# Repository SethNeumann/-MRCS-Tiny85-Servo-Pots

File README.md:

# REPO NAME: MRCS-Tiny85-Servo-Pots

## License: Creative Commons Attribution-NonCommercial-ShareAlike

A simple servo controller to replace Mark Schutzer's PIC based design for which the PIC has become unavbailable.
This controls an SG90 or similar low cost servo. End travel positions are set with 2 pots.  There is a single
input line which is grounded to reverse the turnout. An onboard push button is provided to easy calibration. In
addition to the servo output a LED is provided with onboard limiting resistor.

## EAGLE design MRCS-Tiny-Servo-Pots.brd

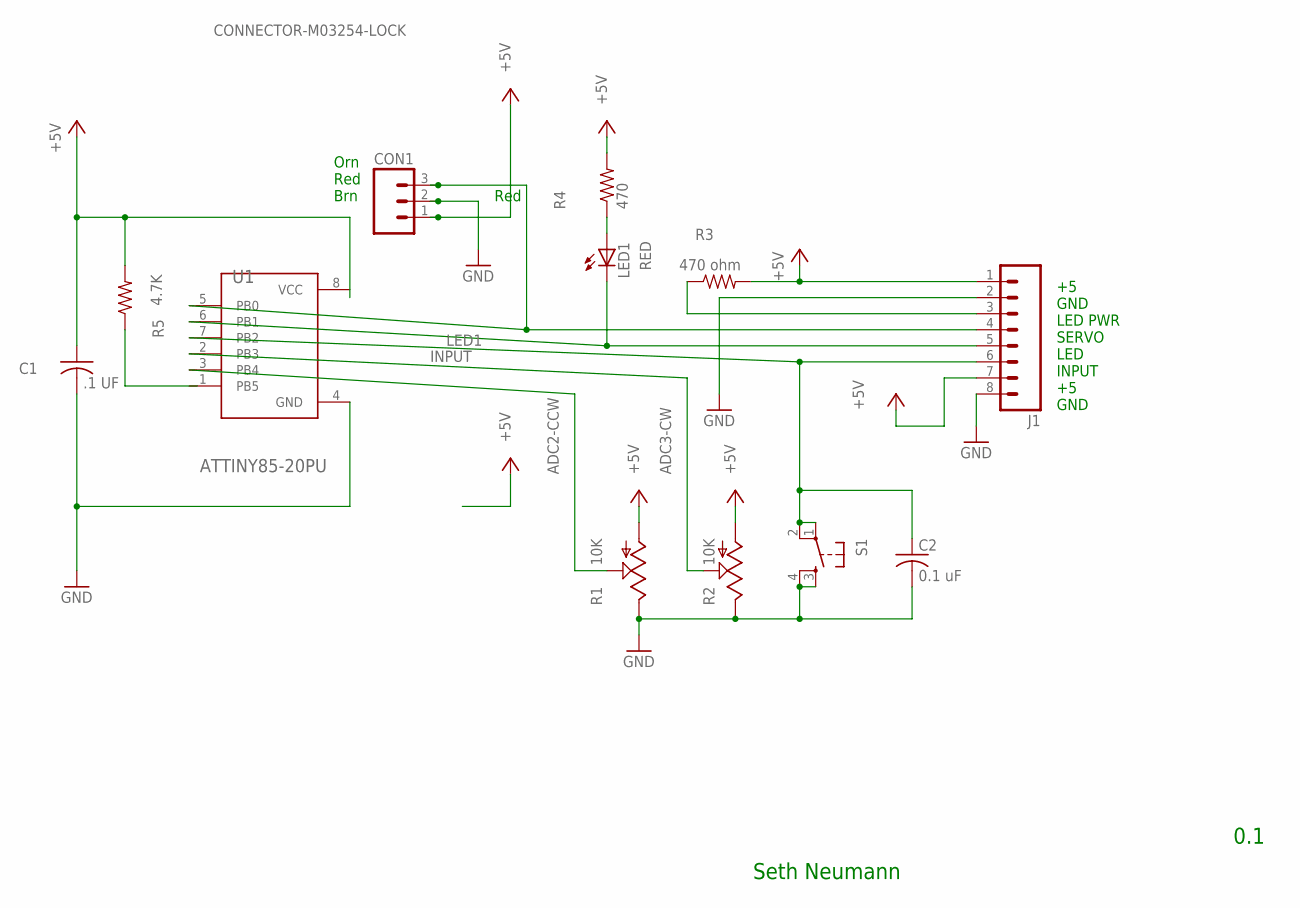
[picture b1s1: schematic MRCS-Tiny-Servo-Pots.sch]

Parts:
C1: .1 UF; C-PTH-0.100
C2: 0.1 uF; C-PTH-0.100
CON1: CONNECTOR-M03254-LOCK; 3POL254
J1: CONNECTOR-M08LOCK; 1X08_LOCK
LED1: RED; LED3MM
R1, R2: 10K; RS3
R3: 470 ohm; AXIAL-0.4-RES
R4: 470; AXIAL-0.4-RES
R5: 4.7K; AXIAL-0.4-RES
S1: TAC_SWITCHPTH; TACTILE-PTH
U1: ATTINY85-20PU; DIP762W46P254L927H533Q8B

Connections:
+5V: C1.1, CON1.1, J1.1, J1.7, R1.A, R2.A, R3.P$2 (2), R4.P$2 (2), R5.P$2 (2)
ADC2-CCW: R1.S, U1.3 (PB4)
ADC3-CW: R2.S, U1.2 (PB3)
GND: C1.2, C2.2, CON1.2, J1.2, J1.8, R1.E, R2.E, S1.3, S1.4, U1.4 (GND)
INPUT: C2.1, J1.6, S1.1, S1.2, U1.7 (PB2)
LED1: J1.5, LED1.K (C), U1.6 (PB1)
unnamed: J1.3, R3.P$1 (1)
unnamed: LED1.A, R4.P$1 (1)
unnamed: CON1.3, J1.4, U1.5 (PB0)
VCC: U1.8 (VCC)

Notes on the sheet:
Seth Neumann
Red
Orn Red Brn
+5 GND LED PWR SERVO LED INPUT +5 GND
0.1

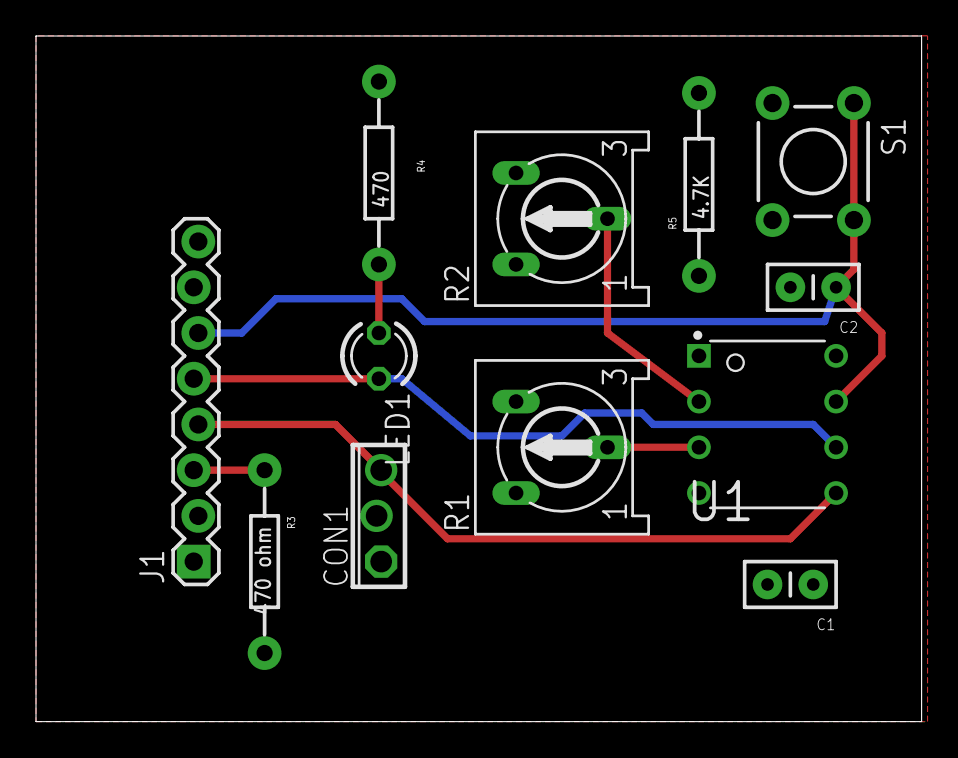
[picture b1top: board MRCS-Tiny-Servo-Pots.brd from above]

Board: 2 copper layers, 49.2 x 38.1 mm, 13 parts (0 on the bottom side), 9 nets.

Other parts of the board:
U$1: MRCSLOGOTOP

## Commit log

2022-03-12 initital commit
2022-03-12 initial commit
    move files from another project in as a baseline
2022-03-30 first pass to production
    this one is a little too big to go 2x3 so some changes will be made, also considering going surface mount, but only 2 resistors and a LED, the rest would be thru hole

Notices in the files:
parts and their libraries:
SparkFun-Electromechanical: Licensing: CC v3.0 Share-Alike You are welcome to use this library for commercial purposes.
